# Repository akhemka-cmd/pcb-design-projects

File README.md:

# PCB Design Projects

A portfolio of my PCB designs — automotive LiDAR hardware (Georgia Tech VIP) and an industrial automation controller (SMARK).

| Project | Description | Tool | Status |
|---|---|---|---|
| [`smark-aem-150dc8-eth`](smark-aem-150dc8-eth/) | STM32-based industrial automation controller with Ethernet, isolated ADC front-end, 8× analog + 8× digital inputs | KiCad | Rev 1 |
| [`automotive-lidar/rev1-sprite-hardware`](automotive-lidar/rev1-sprite-hardware/) | "Project Sprite" automotive LiDAR hardware — interface board, motion platform, power supply, scanning mechanism | KiCad | Rev 1 |
| [`automotive-lidar/rev2-vip-spring25`](automotive-lidar/rev2-vip-spring25/) | Automotive LiDAR redesign — 5-ch receiver, IMU, USB hub, interface & power boards | Altium Designer | Rev 2 |

## Opening the projects

- **KiCad projects** (`smark-aem-150dc8-eth`, `rev1-sprite-hardware`): open the `.kicad_pro` file in KiCad 7/8. Symbol/footprint libraries are referenced via the included `sym-lib-table` / `fp-lib-table` (Rev 1 LiDAR) or KiCad's stock libraries (SMARK).
- **Altium project** (`rev2-vip-spring25`): open `AutoLidar_VIP_Spring25.PrjPcb` in Altium Designer.

## Author

Arnav Khemka — Georgia Institute of Technology

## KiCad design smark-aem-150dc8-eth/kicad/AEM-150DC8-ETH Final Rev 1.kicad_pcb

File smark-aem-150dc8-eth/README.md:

# AEM-150DC8-ETH — SMARK Automation Controller

Industrial automation controller board ("AEM Family") designed for SMARK — a STM32-based I/O controller with Ethernet connectivity and an isolated analog front-end.

## Key features

- **MCU:** STM32F407VETx (ARM Cortex-M4)
- **Ethernet:** LAN8742A PHY + Hanrun HR911105A RJ45 jack, RMII interface (`ETHER_RMII.kicad_sch`)
- **Isolated ADC front-end** (`adc ext.kicad_sch`): ADS1115 16-bit ADC, ISO1540 I2C isolator, RO-0505S isolated DC-DC, LTV-217 optocouplers
- **Signal conditioning:** MCP6004 quad op-amps
- **I/O:** 8× analog inputs (AI1–AI8) and 8× digital inputs (DI1–DI8) on screw terminal blocks
- **Comms & UI:** RS-485 transceiver, 16×4 character LCD, buzzer, status LED
- **Board:** 2-layer, KiCad

## Files

| File | Contents |
|---|---|
| `kicad/AEM-150DC8-ETH Final Rev 1.kicad_pro` | KiCad project — open this |
| `kicad/AEM-150DC8-ETH Final Rev 1.kicad_sch` | Top-level schematic |
| `kicad/AEM-150DC8-ETH Final Rev 1.kicad_pcb` | Board layout |
| `kicad/ETHER_RMII.kicad_sch` | Ethernet PHY hierarchical sheet |
| `kicad/adc ext.kicad_sch` | Isolated external ADC hierarchical sheet |
| `kicad/AEM-150DC8-ETH Final BOM.csv` | Bill of materials |
| `kicad/AEM-150DC8-ETH Final BOM LCSC.csv` | LCSC/JLCPCB assembly BOM |
| `docs/board-3d-render.png` | 3D render of the board |

## Design notes

- Analog and digital sections are partitioned on the layout, with the ADC front-end galvanically isolated from the MCU side.
- The LCSC BOM is set up for JLCPCB assembly (0603 passives throughout).

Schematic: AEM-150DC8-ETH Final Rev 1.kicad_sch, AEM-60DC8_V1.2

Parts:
BZ1: Buzzer; QMB09B03; MPN QMB-09B-03; LCSC_Part C96256
C1: 10uF/50V; C0805; MPN CL21A106KBYQNNE; LCSC_Part C2932476
C2: 100uF/63V; C_Elec_10x10.2; MPN RT1J101M1010; LCSC_Part C280414
C3, C56, C57, C58: 1uF/10V; C0603; MPN CGA0603X5R105K100JT; LCSC_Part C20070307
C4, C5, C6, C7, C9, C13, C14, C15, C16, C19, C20, C21, C22, C24, C27, C28, C29, C30, C31, C32, C33, C34, C37, C38, C39, C40, C42, C48, C54, C55, C59, C60: 0.1uF; C0603
C8, C10, C11: 1uF/100V; C1206; MPN CL31B105KCHNNNE; LCSC_Part C13832
C12: 4.7nF/50V; C0805; MPN TCC0805X7R472M500DT; LCSC_Part C5375827
C17: 6.8pF/100V; C0603; MPN AC0603CRNPO0BN6R8; LCSC_Part C6117724
C18: 100nF/25V; C0805; MPN CGA0805X7R104K250KT; LCSC_Part C36911366
C23, C26, C35: 47uF/10V; C1206; MPN TCC1206X5R476K100HT; LCSC_Part C5449028
C25, C36: 10uF/16V; C0805; MPN GRM21BR61C106KE15L; LCSC_Part C77075
C41, C43: 2.2uF; C0402
C45, C46: 12pF; C0603; MPN CGA0603C0G120J500JT; LCSC_Part C45359931
C65, C66, C69, C70: 0.1uF; C0402; MPN CGA0402X7R104M500GT; LCSC_Part C36911361
C67: 4.7uF/25V; C0402; MPN CGA0402X5R475M250GT; LCSC_Part C6119795
C72: 10uF/16V; C0603; MPN GRM21BR61C106KE15L; LCSC_Part C77075
C73, C74: 12pF; C0402; MPN CGA0603C0G120J500JT; LCSC_Part C45359931
C79, C81: 1uF; C0402; MPN CGA0402X7R104M500GT; LCSC_Part C36911361
C80: 100nF; C0402; MPN CGA0402X7R104M500GT; LCSC_Part C36911361
D1, D2, D5, D7, D9, D10, D15, D16: LED; LED_0603_1608Metric; MPN XL-1608SURC-06; LCSC_Part C965799
D3: SMF33A; SOD-123F; MPN SMF33A; LCSC_Part C2943834
D4: SMAJ30A; D_SMA; MPN SMAJ30A; LCSC_Part C908776
D6: B340A-13-F; DO-214AC; MPN B340A-13-F; LCSC_Part C85098
D8: BZT52C10; D_SOD-123F; MPN BZT52C10V; LCSC_Part C5182291
D11, D12, D13, D14, D37, D38, D39, D40: SMAJ160A; DO-214AC; MPN SMAJ160A; LCSC_Part C2984997
D17, D18, D19, D20, D21, D22, D23, D24: SMF24A; SOD-123F; MPN SMF24A; LCSC_Part C2857282
D25, D26, D27, D28, D42, D43, D44, D45: LESD5Z3.3T1G; SOD-523; MPN LESD5Z3.3T1G; LCSC_Part C136161
D29, D30, D31, D32, D33, D34, D35, D36: 1N4007W; SOD-123F; MPN 1N4007W; LCSC_Part C7528871
D41: SS54; DO-214AC; MPN UMW SS54A; LCSC_Part C2988633
D46: LED; LED_0805_2012Metric; MPN XL-2012SURC; LCSC_Part C22371391
D47: SM712; SOT-23-3; MPN SM712-02HTG; LCSC_Part C172881
D48, D51, D53: SMF3.3A; SOD-123F; MPN SMF3.3A; LCSC_Part C37331473
D49: SMAJ26A; DO-214AC; MPN SMAJ26A; LCSC_Part C42370520
D50: PRTR5V0U2F; FNL6_SOT886_NEX; MPN PRTR5V0U2F,115; LCSC_Part C478118
D52: DSS34; SOD-123F; MPN DSS34; LCSC_Part C49023416
D54: 1N4148WS; SOD-323F; MPN 1N4148WS; LCSC_Part C917117
D55: XL-5050RGBC; LED_RGB_5050-6; MPN XL-5050RGBC; LCSC_Part C2843868
DS1: LCD 16x4; NHD0416BZFLGBW; MPN CH1604C
H2, H3: MountingHole; MountingHole_2.5mm; MPN HP-20M3*20; LCSC_Part C123695
H5, H6, H7, H8: MountingHole; MountingHole_3.5mm; not fitted
J1: Conn_01x02; JST_B2B-XH-A; MPN HX-XH2.54-2PZZ; LCSC_Part C42391660
J2: Screw_Terminal_01x10; TerminalBlock_10P_P5mm; MPN MX128-5.0-10P-GN01-Cu-Y-A; LCSC_Part C5290375
J3: Screw_Terminal_01x09; TerminalBlock_9P_P5mm; MPN MX128-5.0-09P-GN01-Cu-Y-A; LCSC_Part C5290374
J5: CONN_03X2SHROUD; CONN_2X3-SHROUDED_HEADER; MPN 321006SG0ABK00A01; LCSC_Part C601936
J6: Screw_Terminal_01x04; TerminalBlock_Phoenix_MKDS-1,5-4-5.08_1x04_P5.08mm_Horizont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
J7: USB_C_Receptacle_USB2.0_16P; USB_C_Receptacle_G-Switch_GT-USB-7010ASV; MPN HYCW498-USBC16-735B; LCSC_Part C42400252
J8: Screw_Terminal_01x02; TerminalBlock_2P_P5.08mm; MPN MX128L-5.08-02P-GN01-Cu-Y-A; LCSC_Part C5188473
J9: Screw_Terminal_01x02; JST_B2B-XH-A
J10: Screw_Terminal_01x02; CONN2_M22-2010_HRW
L1: MNR8065T100MT; IND_SRN8040TA
Q1: ZXMP6A18KTC; TO-252AA_MOSFET; MPN ZXMP6A18KTC; LCSC_Part C154895
Q5: ES5N10S‎; SOT-23-3; MPN ES5N10S‎; LCSC_Part C39832206
Q6, Q10: BC847; SOT-23-3; MPN BC847C,215; LCSC_Part C8664
Q8, Q13, Q14, Q15, Q16: BSS138; SOT-23-3; MPN BSS138; LCSC_Part C3289984
Q9: DMP4065S-7; SOT-23-3; MPN DMP4065S-7; LCSC_Part C182476
Q11, Q12: 2N7002DW-7-F; SOT-363; MPN 2N7002DW-7-F; LCSC_Part C83571
R1, R45, R46, R47, R48, R49, R50, R51, R52, R71, R84, R85, R87, R90, R94, R97, R99, R102, R110: 10K; R0603; MPN FRC0603J103 TS; LCSC_Part C2930027
R2: 100K; R_0603_1608Metric; MPN FRC0603F1003TS; LCSC_Part C2906980
R3, R5, R9, R58, R62, R64: 1K; R0805; MPN ERJ-HP6F1001V; LCSC_Part C4264406
R6: 1K/1%; R0805; MPN ERJ-HP6F1001V; LCSC_Part C4264406
R7, R11, R134: 470K; R1206
R8, R10, R12: 20.5K; R0805; MPN ERJPB6B1002V; LCSC_Part C161788
R13: 470K/0.1%; R1206
R14: 20.5K/0.1%; R0805; MPN ERJPB6B1002V; LCSC_Part C161788
R15, R16, R17, R18, R19, R20, R21, R22: 3K; R0603; MPN FRC0603J302 TS; LCSC_Part C2907162
R23, R24, R25, R26, R27, R28, R29, R30: 1M; R0603; MPN FRC0603J105 TS; LCSC_Part C2907115
R31, R32, R33, R34, R35, R36, R37, R38, R104, R105, R106: 1K; R0603; MPN FRC0603J102 TS; LCSC_Part C2907113
R39: 28.7K; R0805; MPN FRC0805F2872TS; LCSC_Part C2933395
R40, R41, R42, R43, R67, R68, R69, R70, R88, R107, R109, R112: 100R; R0603; MPN FRC0603J101 TS; LCSC_Part C2907089
R44: 191K; R0603; MPN FRC0603F1913TS; LCSC_Part C2974031
R53, R54, R55, R56, R113, R114, R116, R117, R118, R119, R135: 470K; R_1206_3216Metric
R57, R59, R61: 20.5K; R_0805_2012Metric; MPN ERJPB6B1002V; LCSC_Part C161788
R60: 1K; R_0805_2012Metric; MPN ERJ-HP6F1001V; LCSC_Part C4264406
R63: 20.5K; R_0805_2012Metric_Pad1.20x1.40mm_HandSolder; MPN ERJPB6B1002V; LCSC_Part C161788
R65: 60.4K; R0805; MPN FRC0805F6042TS; LCSC_Part C2933477
R66: 11.5K; R0805; MPN FRC0805F1152TS; LCSC_Part C2933288
R72, R74, R77, R82, R91, R130, R132, R133: 2.2K; R0603; MPN FRC0603J222 TS; LCSC_Part C2907117
R75, R78, R79, R95: 4.7K; R0603; MPN FRC0603J472 TS; LCSC_Part C2907166
R76: 120R; R0603; MPN FRC0603J121 TS; LCSC_Part C2907096
R80, R81: 51R/0.5W; R1206; MPN FRP1206J510 TS; LCSC_Part C7468138
R89: 100K; R0603; MPN FRC0603F1003TS; LCSC_Part C2906980
R92: 22R; R0603; MPN FRC0603J220 TS; LCSC_Part C2907129
R93, R129: 1.5K; R0603; MPN FRC0603J152 TS; LCSC_Part C2907083
R96, R98: 5.1K; R0603; MPN FRC0603J512 TS; LCSC_Part C2907114
R108: 150R; R0603; MPN FRC0603F1500TS; LCSC_Part C2906994
R111: 100R; R0805; MPN FRS0805J101 TS; LCSC_Part C7467912
R115: 470K/0.1%; R_1206_3216Metric
R124: 0R; R0603
R137, R138: 2.2K; R0603
R139, R140, R141: 10K; R0603
RV1: 10K; Pot_TRIM_3362P-1-103LF; MPN 3362P-1-103LF; LCSC_Part C118956
SW1, SW3: KH-303015-AJ; SW4_CS1210F260_3.4mm; MPN KH-303015-AJ; LCSC_Part C530668
SW2: SW_DIP_x04; MPN DA-04RP; LCSC_Part C129023
Switch_PCB1: Switch_PCB
TP1: GND; TestPoint_Pad_D1.0mm; not fitted
TP2: +5V; TestPoint_Pad_D1.0mm; not fitted
TP3: +3V3; TestPoint_Pad_D1.0mm; not fitted
U1: MC7805BDTRKG-GK; TO-252-2; MPN MC7805BDTRKG-GK; LCSC_Part C46061589
U2, U14: MCP6004; SOIC-14; MPN MCP6004T-I/SL; LCSC_Part C20627194
U3, U4: LTV-847S; SMDIP-16_W9.53mm; MPN LTV-847S; LCSC_Part C114599
U5: TPS54360DDAR; TI_SO-PowerPAD-8_ThermalVias; MPN TPS54360DDAR; LCSC_Part C44377
U6, U7, U8, U9, U10, U11, U12, U13: 74LVC1G14GW; TSSOP-5; MPN 74LVC1G14GW,125; LCSC_Part C19829653
U15: NCP1117ST33T3G; SOT-223-3_TabPin2; MPN NCP1117ST33T3G; LCSC_Part C26537
U16: CAT24C16TDI-GT3; SOT-753; MPN CAT24C16TDI-GT3; LCSC_Part C605329
U17: THVD1500DR; SOIC-8N_127P599X175; MPN THVD1500DR; LCSC_Part C191014
U20: W25N512GVEIG; SON127P800X600X80-9N-D; MPN W25N512GVEIG; LCSC_Part C3024446
U21: W25Q512JVSSIQ; SOIC-8N_127P790X216; not fitted
U22: PCA9557PW; TSSOP-16; MPN PCA9557PW,118; LCSC_Part C141380
U23: STM32F407VETx; LQFP-100_14x14mm_P0.5mm; MPN STM32F407VET6; LCSC_Part C28730
Y2: M16000E134; SMD3225-4P; MPN M16000E134; LCSC_Part C258943
Y4: SMD_CRYSTAL32.768; XTAL_NX2012SA-32.768K-STD-MUB-1; MPN NX2012SA-32.768KHZ-STD-MUB-2; LCSC_Part C891748

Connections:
10-30VDC: C2.1, C8.1, C10.1, C11.1, D8.1 (K), Q1.2 (S), U5.2 (VIN)
+3.3V: C65.1, C66.1, C67.1, C69.1, C70.1, C79.1, C80.1, C81.1, R124.2, U23.11 (VDD), U23.19 (VDD), U23.21 (VREF+), U23.22 (VDDA), U23.28 (VDD), U23.50 (VDD), U23.75 (VDD), U23.100 (VDD)
+3.3VA: C9.1, C24.1, U2.4 (V+), U14.4 (V+); also elsewhere on the board
+3V3: C27.1, C28.1, C29.1, C30.1, C31.1, C32.1, C33.1, C34.1, C36.1, C42.1, C54.2, J1.2, Q8.1 (G), Q13.1 (G), Q14.1 (G), Q15.1 (G), Q16.1 (G), R45.1, R46.1, R47.1, R48.1, R49.1, R50.1, R51.1, R52.1, R72.1, R77.1, R84.1, R87.1, R90.2, R91.1, R97.2, R99.2, R124.1, R132.2, R133.1, R139.1, R140.1, R141.1, SW1.3, SW1.4, TP3.1 (1_1), U6.5 (VCC), U7.5 (VCC), U8.5 (VCC), U9.5 (VCC), U10.5 (VCC), U11.5 (VCC), U12.5 (VCC), U13.5 (VCC), U15.2 (VO), U16.4 (V_{CC}), U20.7 (/HOLD_(IO3)), U20.8 (VCC), U21.7 (/HOLD_OR_/RESET_(IO3)), U21.8 (VCC); also elsewhere on the board
+5V: BZ1.1 (+), C23.1, C25.1, C26.1, C35.1, C48.1, C59.1, C60.1, D54.1 (K), D55.4 (GA), D55.5 (RA), D55.6 (BA), DS1.2 (VDD), L1.2, Q9.2 (S), R65.1, R71.1, R74.1, R75.1, R78.1, R82.1, R94.2, R95.1, R102.1, R111.1, R137.1, R138.1, RV1.1, TP2.1 (1_1), U15.3 (VI), U17.8 (VCC), U22.16 (VDD); also elsewhere on the board
+5V_DI: C3.1, D1.2 (A), D2.2 (A), D5.2 (A), D7.2 (A), D9.2 (A), D10.2 (A), D15.2 (A), D16.2 (A), R23.1, R24.1, R25.1, R26.1, R27.1, R28.1, R29.1, R30.1, U1.3 (OUT), U3.1, U3.3, U3.5, U3.7, U4.1, U4.3, U4.5, U4.7
AI1: C13.1, R40.1; also elsewhere on the board
AI2: C14.1, R41.1; also elsewhere on the board
AI3: C15.1, R42.1; also elsewhere on the board
AI4: C16.1, R43.1; also elsewhere on the board
AI5: C40.1, R70.1; also elsewhere on the board
AI6: C37.1, R67.1; also elsewhere on the board
AI7: C38.1, R68.1; also elsewhere on the board
AI8: C39.1, R69.1; also elsewhere on the board
AI-1: D11.1 (A1), J3.2, R113.1
AI-2: D12.1 (A1), J3.3, R135.1
AI-3: D13.1 (A1), J3.4, R114.1
AI-4: D14.1 (A1), J3.5, R115.1
AI-5: D38.1 (A1), J3.6, R116.1
AI-6: D39.1 (A1), J3.7, R117.1
AI-7: D40.1 (A1), J3.8, R118.1
AI-8: D37.1 (A1), J3.9, R119.1
BOOT0: R85.1, SW1.1, SW1.2, U23.94 (BOOT0)
B_LED: R104.1, U23.2 (PE3)
Buzzer: R129.1, U23.63 (PC6)
CLK+: C46.1, U23.12 (PH0), Y2.1
CLK-: C45.1, U23.13 (PH1), Y2.3
COL1: U23.17 (PC2); also elsewhere on the board
COL2: U23.18 (PC3); also elsewhere on the board
COM-DO_PLC-0V: D49.2 (A2), J8.1, Q5.2 (S)
D4: DS1.11 (DB4), U22.11 (IO4)
D5: DS1.12 (DB5), U22.12 (IO5)
D6: DS1.13 (DB6), U22.13 (IO6)
D7: DS1.14 (DB7), U22.14 (IO7)
D+: D50.3, J7.A6 (D+), J7.B6 (D+)
D-: D50.1, J7.A7 (D-), J7.B7 (D-)
DI1: D21.1 (A1), J2.3, R15.2
DI1_LED: D1.1 (K), D29.2 (A), R23.2, R31.2
DI2: D17.1 (A1), J2.4, R16.2
DI2_LED: D2.1 (K), D30.2 (A), R24.2, R32.2
DI3: D22.1 (A1), J2.5, R17.2
DI3_LED: D5.1 (K), D31.2 (A), R25.2, R33.2
DI4: D18.1 (A1), J2.6, R18.2
DI4_LED: D7.1 (K), D32.2 (A), R26.2, R34.2
DI5: D23.1 (A1), J2.7, R19.2
DI5_LED: D9.1 (K), D33.2 (A), R27.2, R35.2
DI6: D19.1 (A1), J2.8, R20.2
DI6_LED: D10.1 (K), D34.2 (A), R28.2, R36.2
DI7: D24.1 (A1), J2.9, R21.2
DI7_LED: D15.1 (K), D35.2 (A), R29.2, R37.2
DI8: D20.1 (A1), J2.10, R22.2
DI8_LED: D16.1 (K), D36.2 (A), R30.2, R38.2
DI-1: R45.2, U3.16, U6.2
DI-2: R46.2, U3.14, U7.2
DI-3: R47.2, U3.12, U8.2
DI-4: R48.2, U3.10, U9.2
DI-5: R49.2, U4.16, U10.2
DI-6: R50.2, U4.14, U11.2
DI-7: R51.2, U4.12, U12.2
DI-8: R52.2, U4.10, U13.2
DIP_S1: R141.2, SW2.2B, U23.81 (PD0)
DIP_S2: R140.2, SW2.3B, U23.82 (PD1)
DIP_S3: R139.2, SW2.4B, U23.83 (PD2)
DI_1: U6.4, U23.39 (PE8)
DI_2: U7.4, U23.40 (PE9)
DI_3: U8.4, U23.41 (PE10)
DI_4: U9.4, U23.54 (PB15)
DI_5: U10.4, U23.43 (PE12)
DI_6: U11.4, U23.44 (PE13)
DI_7: U12.4, U23.45 (PE14)
DI_8: U13.4, U23.46 (PE15)
DO-ALARM: D49.1 (A1), J8.2, R92.2
DO_1: R88.1, U23.88 (PD7)
E: DS1.6 (E), U22.7 (IO1)
FLASH_CS: U20.1 (/CS), U21.1 (/CS), U23.77 (PA15)
Field_VTG: D3.1 (A1), D6.2 (A), J2.2
GND: C2.2, C8.2, C10.2, C11.2, C12.2, C17.2, C23.2, C25.2, C26.2, C27.2, C28.2, C29.2, C30.2, C31.2, C32.2, C33.2, C34.2, C35.2, C36.2, C41.2, C42.2, C43.2, C45.2, C46.2, C48.2, C54.1, C55.1, C56.2, C57.2, C58.2, C59.2, C60.2, C65.2, C66.2, C67.2, C69.2, C70.2, C72.1, C73.2, C74.2, C79.2, C80.2, C81.2, D4.2 (A2), D41.2 (A), D46.1 (K), D47.3 (common), D48.2 (A2), D50.2, D51.2 (A2), D53.2 (A2), DS1.1 (VSS), J5.6, J6.3, J7.A1 (GND), J7.A12 (GND), J7.B1 (GND), J7.B12 (GND), J7.S1 (SHIELD), J9.1, J10.1, Q10.2 (E), Q11.1 (S1), Q11.4 (S2), Q12.1 (S1), Q12.4 (S2), R1.2, R2.2, R44.2, R66.2, R79.2, R85.2, R89.2, R93.1, R96.1, R98.1, R110.1, R130.2, RV1.3, SW2.2A, SW2.3A, SW2.4A, SW3.3, SW3.4, Switch_PCB1.4 (GND), TP1.1 (1_1), U3.9, U3.11, U3.13, U3.15, U4.9, U4.11, U4.13, U4.15, U5.7 (GND), U5.9 (GNDPAD), U6.3 (GND), U7.3 (GND), U8.3 (GND), U9.3 (GND), U10.3 (GND), U11.3 (GND), U12.3 (GND), U13.3 (GND), U15.1 (GND), U16.2 (V_{SS}), U17.5 (GND), U20.4 (GND), U20.9 (EP), U21.4 (GND), U22.3 (A0), U22.4 (A1), U22.5 (A2), U22.8 (VSS), U23.10 (VSS), U23.20 (VSSA), U23.27 (VSS), U23.74 (VSS), U23.99 (VSS), Y2.2, Y2.4; also elsewhere on the board
GND2: C1.2, C3.2, D3.2 (A2), D17.2 (A2), D18.2 (A2), D19.2 (A2), D20.2 (A2), D21.2 (A2), D22.2 (A2), D23.2 (A2), D24.2 (A2), J2.1, U1.2 (GND)
GND_ISO: C4.2, C5.2, C6.2, C7.2, C9.2, C13.2, C14.2, C15.2, C16.2, C19.2, C20.2, C21.2, C22.2, C24.2, C37.2, C38.2, C39.2, C40.2, D11.2 (A2), D12.2 (A2), D13.2 (A2), D14.2 (A2), D25.2 (A2), D26.2 (A2), D27.2 (A2), D28.2 (A2), D37.2 (A2), D38.2 (A2), D39.2 (A2), D40.2 (A2), D42.2 (A2), D43.2 (A2), D44.2 (A2), D45.2 (A2), J3.1, R8.2, R10.2, R12.2, R14.2, R57.2, R59.2, R61.2, R63.2, U2.11 (V-), U14.11 (V-); also elsewhere on the board
G_LED: R106.1, U23.1 (PE2)
I2C1_SCL: Q16.2 (S), R133.2, U16.1 (SCL), U23.95 (PB8)
I2C1_SCL_5V: Q16.3 (D), R137.2, U22.1 (SCL)
I2C1_SDA: Q13.2 (S), R132.1, U16.3 (SDA), U23.93 (PB7)
I2C1_SDA_5V: Q13.3 (D), R138.2, U22.2 (SDA)
IO_RESET: Q8.2 (S), R91.2, U23.5 (PE6)
IO_RESET_5V: Q8.3 (D), R95.2, U22.15 (~RESET)
LCD_Backlight: R112.1, U23.92 (PB6)
NRST: C55.2, J5.4, R87.2, SW3.1, SW3.2, U23.14 (NRST)
NTC: J1.1, R1.1, U23.65 (PC8)
unnamed: BZ1.2 (-), D54.2 (A), Q10.3 (C)
unnamed: C12.1, R39.2
unnamed: D4.1 (A1), J6.4, Q1.3 (D)
unnamed: C1.1, D6.1 (K), U1.1 (IN)
unnamed: D8.2 (A), Q1.1 (G), R2.1
unnamed: C4.1, D25.1 (A1), R3.1, U2.3 (+)
unnamed: C5.1, D26.1 (A1), R9.1, U2.5 (+)
unnamed: C6.1, D27.1 (A1), R5.1, U2.10 (+)
unnamed: C7.1, D28.1 (A1), R6.1, U2.12 (+)
unnamed: D29.1 (K), R15.1
unnamed: D30.1 (K), R16.1
unnamed: D31.1 (K), R17.1
unnamed: D32.1 (K), R18.1
unnamed: D33.1 (K), R19.1
unnamed: D34.1 (K), R20.1
unnamed: D35.1 (K), R21.1
unnamed: D36.1 (K), R22.1
unnamed: C18.1, D41.1 (K), L1.1, U5.8 (SW)
unnamed: C19.1, D42.1 (A1), R60.1, U14.3 (+)
unnamed: C20.1, D43.1 (A1), R62.1, U14.5 (+)
unnamed: C21.1, D44.1 (A1), R64.1, U14.10 (+)
unnamed: C22.1, D45.1 (A1), R58.1, U14.12 (+)
unnamed: D46.2 (A), R71.2
unnamed: D52.1 (K), J7.A4 (VBUS), J7.A9 (VBUS), J7.B4 (VBUS), J7.B9 (VBUS)
unnamed: D55.1 (BK), R107.2
unnamed: D55.3 (GK), R109.2
unnamed: D55.2 (RK), R108.2
unnamed: DS1.15 (LED+), R111.2
unnamed: DS1.16 (LED-), Q12.3 (D2)
unnamed: DS1.3 (V0), RV1.2
unnamed: J7.A5 (CC1), R96.2
unnamed: J7.B5 (CC2), R98.2
unnamed: C72.2, J9.2, J10.2, U23.6 (VBAT)
unnamed: Q5.3 (D), R92.1
unnamed: Q5.1 (G), R88.2, R89.1
unnamed: Q6.3 (C), Q9.1 (G), R94.1
unnamed: Q6.2 (E), R93.2
unnamed: Q10.1 (B), R129.2
unnamed: Q11.6 (D1), R108.1
unnamed: Q11.2 (G1), R105.2
unnamed: Q11.3 (D2), R107.1
unnamed: Q11.5 (G2), R104.2
unnamed: Q12.6 (D1), R109.1
unnamed: Q12.2 (G1), R106.2
unnamed: Q12.5 (G2), R110.2, R112.2
unnamed: R3.2, R7.2, R8.1
unnamed: R9.2, R10.1, R134.2
unnamed: R11.1, R114.2
unnamed: R5.2, R11.2, R12.1
unnamed: R6.2, R13.2, R14.1
unnamed: R31.1, U3.2
unnamed: R32.1, U3.4
unnamed: R33.1, U3.6
unnamed: R34.1, U3.8
unnamed: R35.1, U4.2
unnamed: R36.1, U4.4
unnamed: R37.1, U4.6
unnamed: R38.1, U4.8
unnamed: R53.2, R57.1, R58.2
unnamed: R54.2, R59.1, R60.2
unnamed: R55.2, R61.1, R62.2
unnamed: R56.2, R63.1, R64.2
unnamed: R7.1, R113.2
unnamed: R13.1, R115.2
unnamed: R54.1, R116.2
unnamed: R55.1, R117.2
unnamed: R56.1, R118.2
unnamed: R53.1, R119.2
unnamed: R134.1, R135.2
unnamed: R40.2, U2.1, U2.2 (-)
unnamed: R41.2, U2.6 (-), U2.7
unnamed: R42.2, U2.8, U2.9 (-)
unnamed: R43.2, U2.13 (-), U2.14
unnamed: C18.2, U5.1 (BOOT)
unnamed: C17.1, R39.1, U5.6 (COMP)
unnamed: R65.2, R66.1, U5.5 (FB)
unnamed: R44.1, U5.4 (RT/CLK)
unnamed: R70.2, U14.1, U14.2 (-)
unnamed: R67.2, U14.6 (-), U14.7
unnamed: R68.2, U14.8, U14.9 (-)
unnamed: R69.2, U14.13 (-), U14.14
unnamed: R130.1, U16.5 (WP)
unnamed: R76.1, R78.2, R80.1, U17.6 (A)
unnamed: R84.2, U20.3 (/WP_(IO2)), U21.3 (/WP_(IO2))
unnamed: C74.1, U23.8 (PC14), Y4.1
unnamed: C73.1, U23.9 (PC15), Y4.2
unnamed: C41.1, U23.49 (VCAP_1)
unnamed: C43.1, U23.73 (VCAP_2)
PWRC_USB: Q6.1 (B), U23.69 (PA10)
RMII_CRS_DV: U23.32 (PA7); also elsewhere on the board
RMII_MDC: U23.16 (PC1); also elsewhere on the board
RMII_MDIO: U23.25 (PA2); also elsewhere on the board
RMII_REF_CLK: U23.24 (PA1); also elsewhere on the board
RMII_RXD0: U23.33 (PC4); also elsewhere on the board
RMII_RXD1: U23.34 (PC5); also elsewhere on the board
RMII_TXD0: U23.51 (PB12); also elsewhere on the board
RMII_TXD1: U23.52 (PB13); also elsewhere on the board
RMII_TX_EN: U23.48 (PB11); also elsewhere on the board
RS: DS1.4 (RS), R102.2, U22.6 (IO0)
RS485-1B_TRO: R76.2, SW2.1B
RS485-1_TRC: R79.1, R81.2, SW2.1A, U17.7 (B)
RS485_1A: D47.1 (A1), J6.1, R80.2
RS485_1B: D47.2 (A2), J6.2, R81.1
RS485_EN: Q14.2 (S), R72.2, U23.4 (PE5)
RS485_EN_5V: Q14.3 (D), R74.2, U17.2 (~RE), U17.3 (DE)
R_LED: R105.1, U23.3 (PE4)
R/W: DS1.5 (R/W), U22.9 (IO2)
SCL2: U23.67 (PA8); also elsewhere on the board
SDA2: U23.66 (PC9); also elsewhere on the board
SPI1_MISO: U20.2 (DO_(IO1)), U21.2 (DO_(IO1)), U23.90 (PB4)
SPI1_MOSI: U20.5 (DI_(ID0)), U21.5 (DI_(ID0)), U23.91 (PB5)
SPI1_SCK: U20.6 (CLK), U21.6 (CLK), U23.89 (PB3)
SWC: J5.1, U23.76 (PA14)
SWD: J5.2, U23.72 (PA13)
U2_RX: J5.3, U23.87 (PD6)
U2_TX: J5.5, U23.86 (PD5)
U3_RX: R75.2, U17.1 (RO), U23.79 (PC11)
U3_TX: Q15.2 (S), R77.2, U23.78 (PC10)
U3_TX_5V: Q15.3 (D), R82.2, U17.4 (DI)
USB_D+: D50.4, U23.71 (PA12)
USB_D-: D50.6, U23.70 (PA11)
USB_VBUS: D50.5, D52.2 (A), Q9.3 (D), U23.68 (PA9)
USW1: C56.1, D48.1 (A1), R90.1, Switch_PCB1.1 (SW1), U23.62 (PD15)
USW2: C57.1, D51.1 (A1), R97.1, Switch_PCB1.2 (SW2), U23.61 (PD14)
USW3: C58.1, D53.1 (A1), R99.1, Switch_PCB1.3 (SW3), U23.60 (PD13)

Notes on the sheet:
NTC
DIP Switch
RTC
DIGITAL OUTPUT
RST SWITCH
ANALOG INPUTS
EEPROM
Programmer
LDO
RS-485
Output: 5V/2A
SPI FLASH
DIGITAL INPUTS
LCD 16x4 DISPLAY
12V/24V
USER SWITCHES
BUZZER
Float to Enable
USB TYPE-C
POWER SUPPLY
MICROCONTROLLER
Change buzzer part no.
Input Supply: 10V-30VDC Output: 5V/2A
I/O Expander
Using as normal GPIO Pin
RGB LED
PWR LED
(PLC +24V)
DO-ALARM
PLC 0V

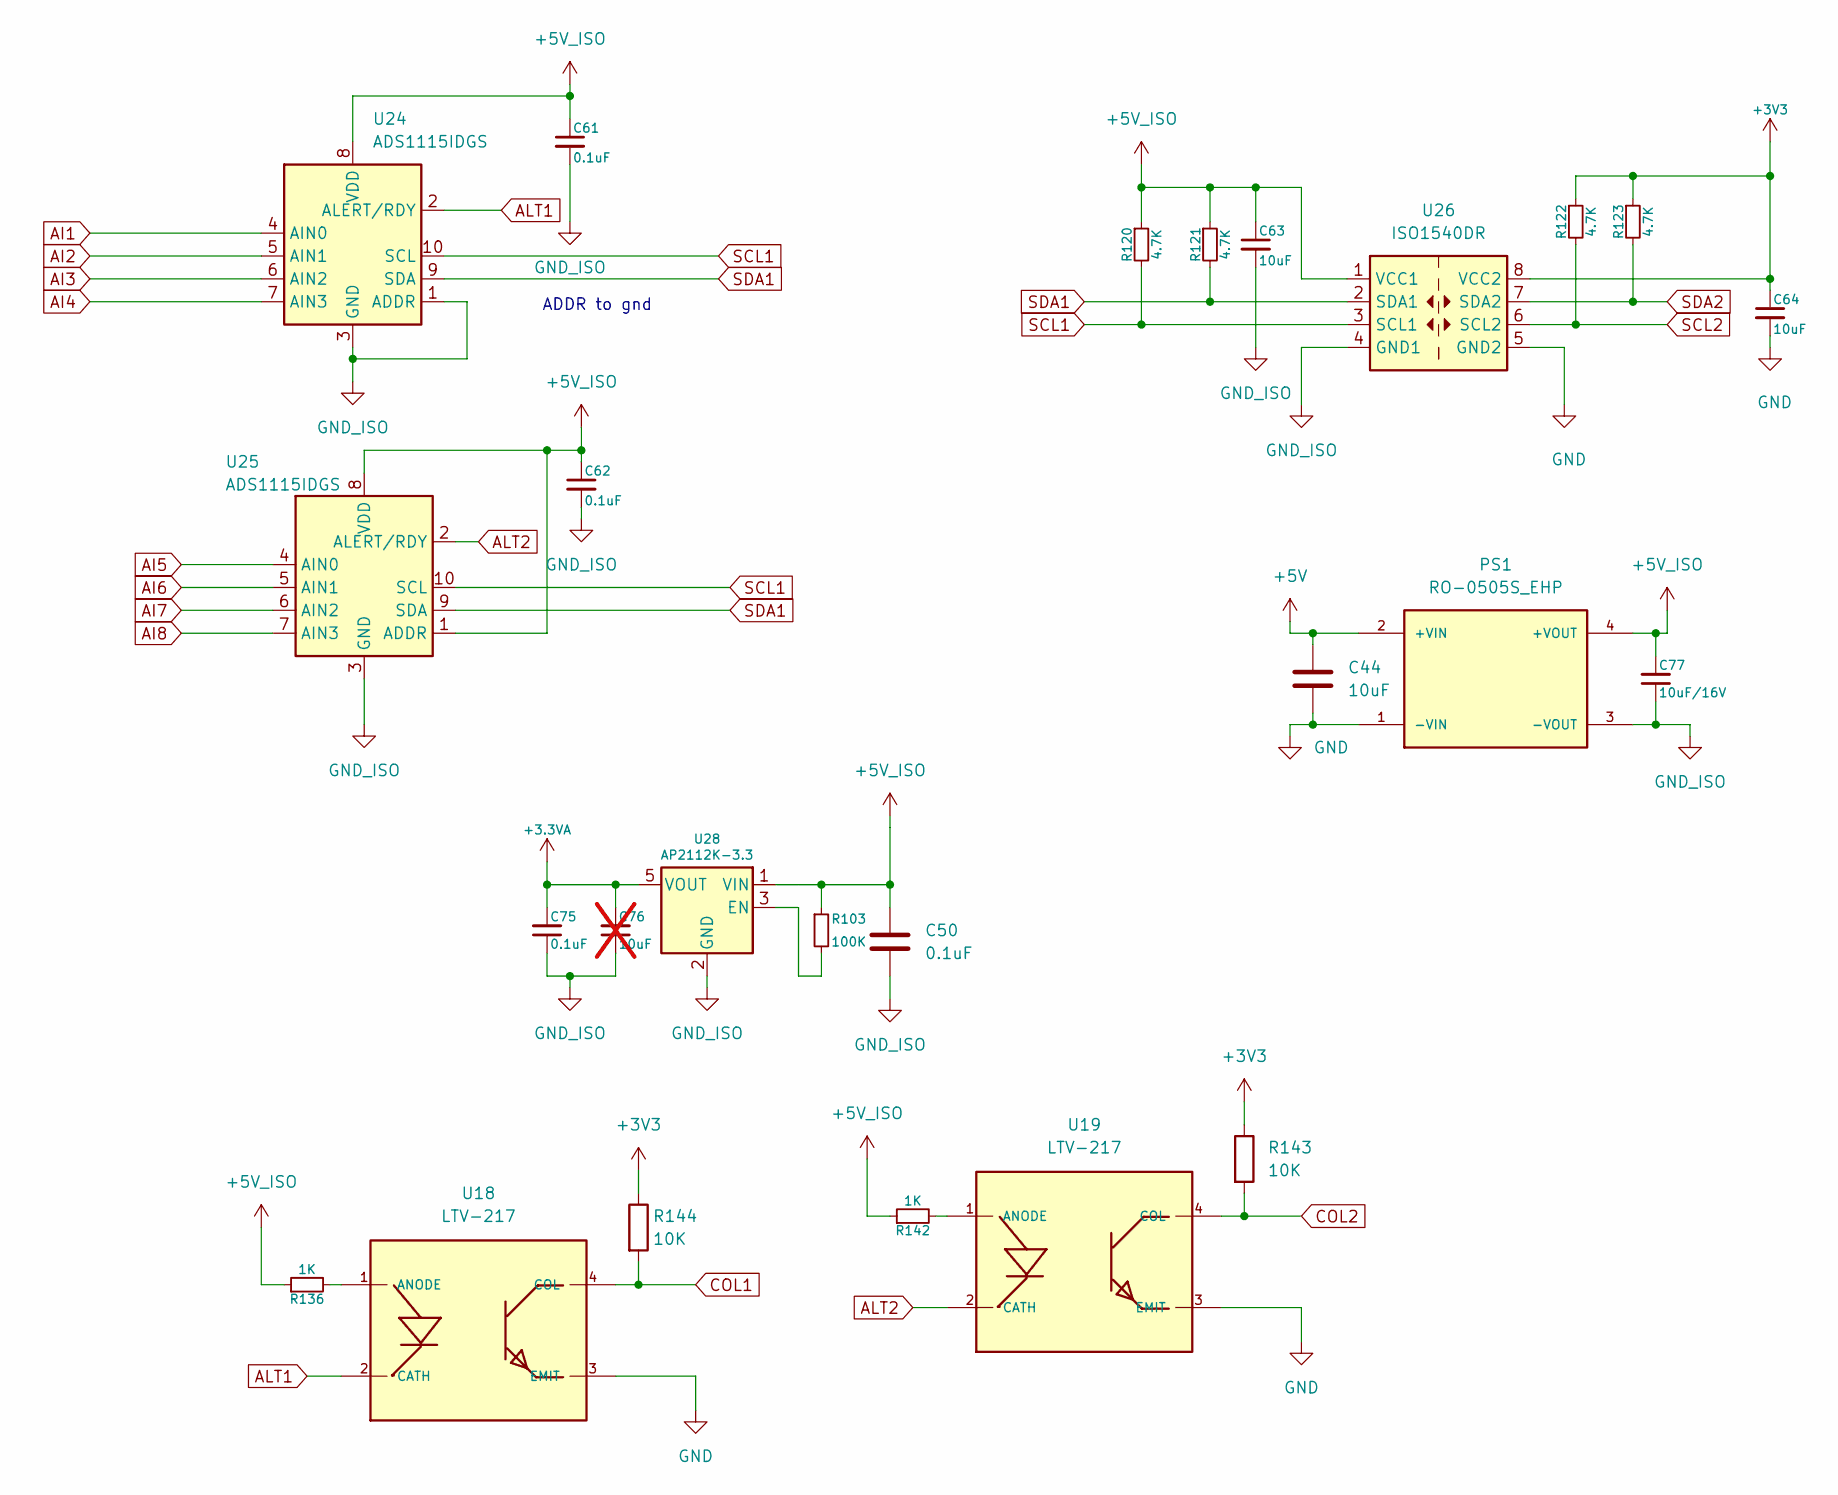
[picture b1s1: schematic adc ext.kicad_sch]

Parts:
C44: 10uF; C0805
C50: 0.1uF; C0805
C61, C75: 0.1uF; C0603
C62: 0.1uF; C0402; MPN CGA0603X7R104K500JT; LCSC_Part C6119867
C63: 10uF; C0603; MPN CGA0603X7R104K500JT; LCSC_Part C6119867
C64: 10uF; C0402; MPN CGA0603X7R104K500JT; LCSC_Part C6119867
C76: 10uF; C0603; MPN FCC0603X106M6R3CT; LCSC_Part C5137483; not fitted
C77: 10uF/16V; C0805; MPN GRM21BR61C106KE15L; LCSC_Part C77075
PS1: RO-0505S_EHP; CONV_RO-0505S_H; PARTREV 1; LCSC_Part C22372152
R103: 100K; R0603; MPN FRC0603F1003TS; LCSC_Part C2906980
R120, R121, R122, R123: 4.7K; R0603; MPN ERJ-HP6F1001V; LCSC_Part C4264406
R136, R142: 1K; R0603; MPN ERJ-HP6F1001V; LCSC_Part C4264406
R143, R144: 10K; R0603
U18: LTV-217; MPN LTV217; DIGIKEY 160-2238-1-ND
U19: LTV-217; MPN LTV-217-C-G; DIGIKEY 160-2238-1-ND
U24, U25: ADS1115IDGS; TSSOP-10_3x3mm_P0.5mm; MPN ADS1115IDGS
U26: ISO1540DR; SOIC-8_3.9x4.9mm_P1.27mm; MPN ISO1540DR
U28: AP2112K-3.3; SOT-753; MPN AP2112K-3.3TRG1; LCSC_Part C23380830

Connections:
+3.3VA: C75.2, C76.2, U28.5 (VOUT); also elsewhere on the board
+3V3: C64.1, R122.1, R123.1, R143.1, R144.1, U26.8 (VCC2); also elsewhere on the board
+5V: C44.1, PS1.2 (+VIN); also elsewhere on the board
+5V_ISO: C50.1, C61.1, C62.1, C63.1, C77.2, PS1.4 (+VOUT), R103.1, R120.1, R121.1, R136.1, R142.1, U24.8 (VDD), U25.1 (ADDR), U25.8 (VDD), U26.1 (VCC1), U28.1 (VIN)
AI1: U24.4 (AIN0); also elsewhere on the board
AI2: U24.5 (AIN1); also elsewhere on the board
AI3: U24.6 (AIN2); also elsewhere on the board
AI4: U24.7 (AIN3); also elsewhere on the board
AI5: U25.4 (AIN0); also elsewhere on the board
AI6: U25.5 (AIN1); also elsewhere on the board
AI7: U25.6 (AIN2); also elsewhere on the board
AI8: U25.7 (AIN3); also elsewhere on the board
ALT1: U18.2 (CATH), U24.2 (ALERT/RDY)
ALT2: U19.2 (CATH), U25.2 (ALERT/RDY)
COL1: R144.2, U18.4 (COL); also elsewhere on the board
COL2: R143.2, U19.4 (COL); also elsewhere on the board
GND: C44.2, C64.2, PS1.1 (-VIN), U18.3 (EMIT), U19.3 (EMIT), U26.5 (GND2); also elsewhere on the board
GND_ISO: C50.2, C61.2, C62.2, C63.2, C75.1, C76.1, C77.1, PS1.3 (-VOUT), U24.1 (ADDR), U24.3 (GND), U25.3 (GND), U26.4 (GND1), U28.2 (GND); also elsewhere on the board
unnamed: R136.2, U18.1 (ANODE)
unnamed: R142.2, U19.1 (ANODE)
unnamed: R103.2, U28.3 (EN)
SCL1: R120.2, U24.10 (SCL), U25.10 (SCL), U26.3 (SCL1)
SCL2: R122.2, U26.6 (SCL2); also elsewhere on the board
SDA1: R121.2, U24.9 (SDA), U25.9 (SDA), U26.2 (SDA1)
SDA2: R123.2, U26.7 (SDA2); also elsewhere on the board

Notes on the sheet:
ADDR to gnd

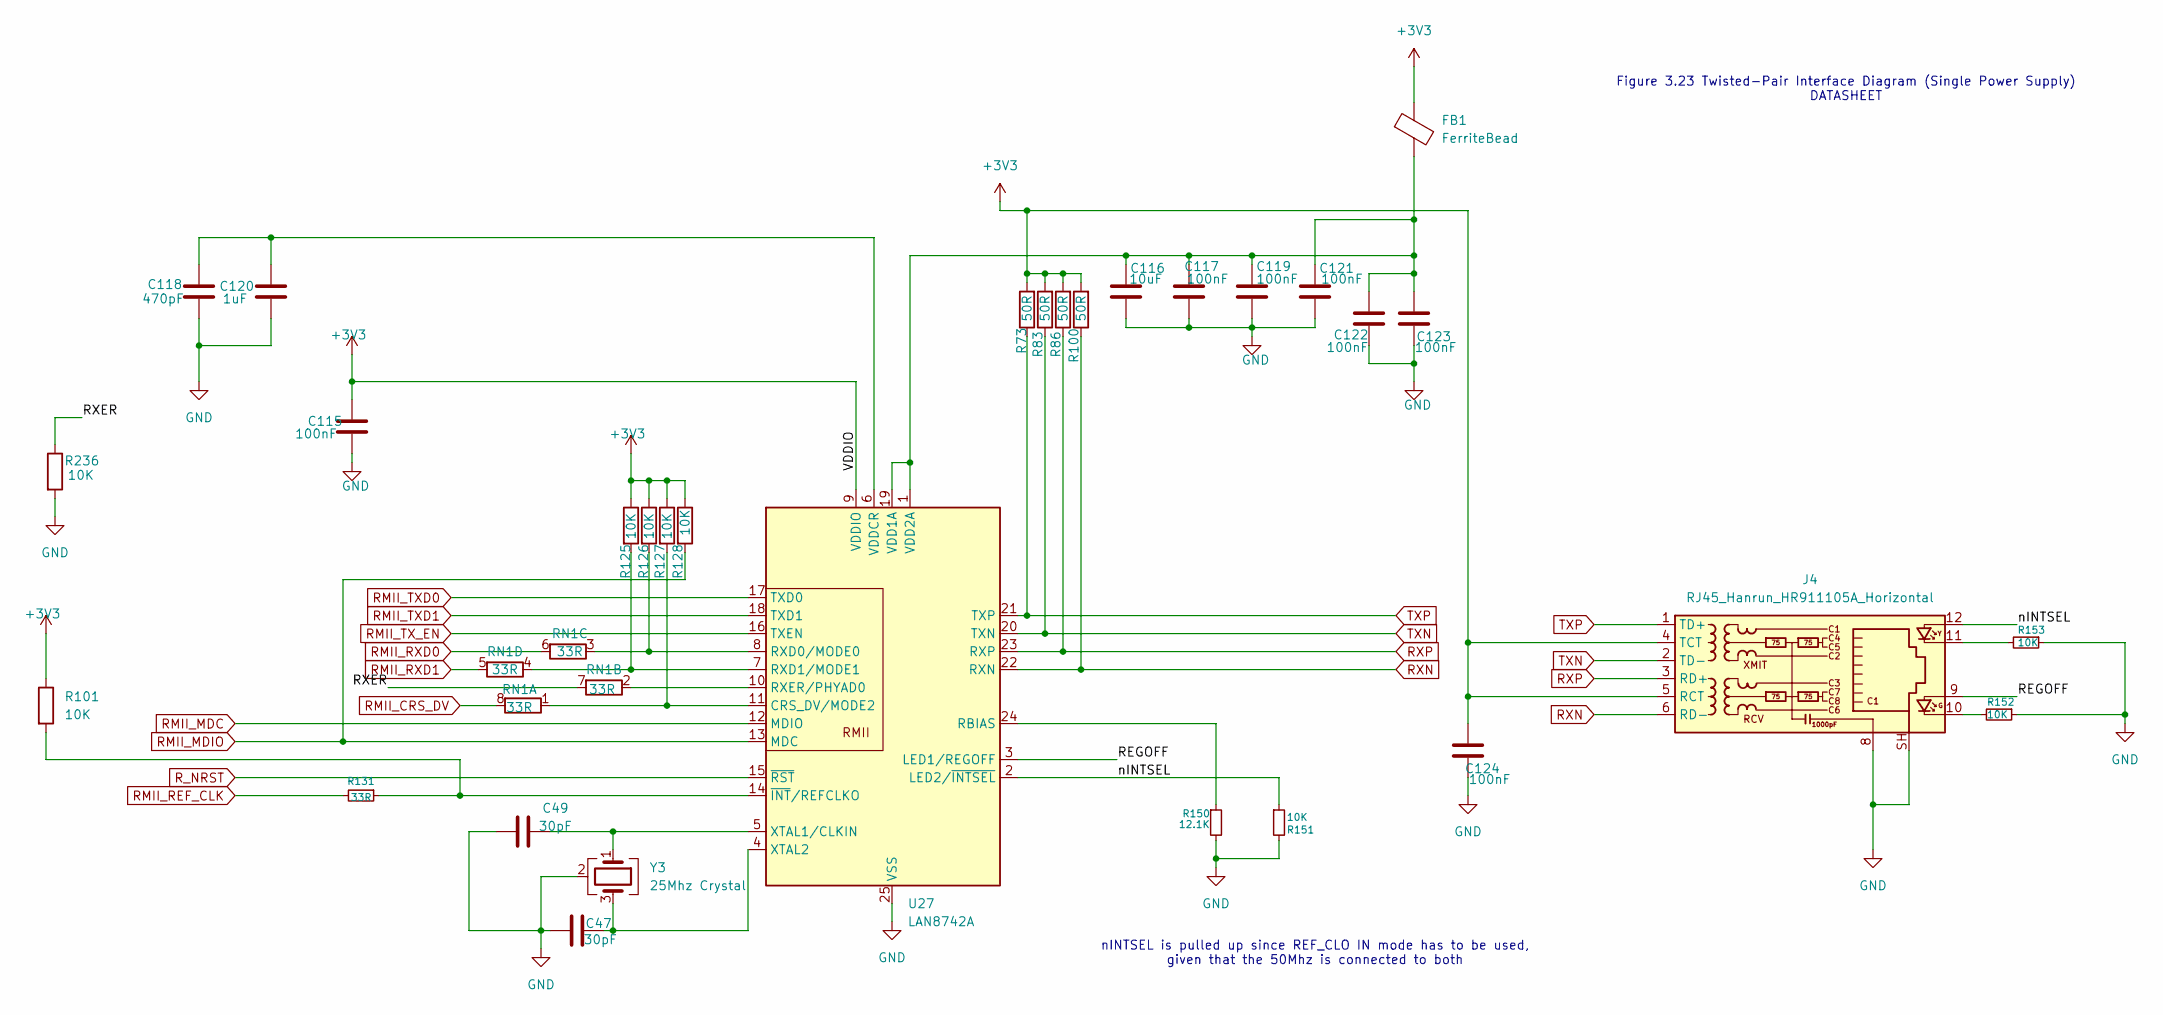
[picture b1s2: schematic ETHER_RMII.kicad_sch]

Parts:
C47, C49: 30pF; C0603
C115, C117, C119, C121, C122, C123: 100nF; C0402
C116: 10uF; C0402; LCSC_Part C6119867
C118: 470pF; C0402
C120: 1uF; C0402
C124: 100nF; C0603
FB1: FerriteBead; R0805
J4: RJ45_Hanrun_HR911105A_Horizontal; MPN HR911105A; LCSC_Part C12074
R73, R83, R86, R100: 50R; R0603
R101, R125, R126, R127, R128, R236: 10K; R0603
R131: 33R; R0603
R150: 12.1K; R_0402_1005Metric
R151: 10K; R_0402_1005Metric
R152, R153: 10K; R0603; MPN FRC0603J472 TS; LCSC_Part C2907166
RN1: 33R; CAT16-1206_8L
U27: LAN8742A; VQFN-24-1EP_4x4mm_P0.5mm_EP2.5x2.5mm_ThermalVias; MPN LAN8742A
Y3: 25Mhz Crystal; Crystal_SMD_3225-4Pin_3.2x2.5mm; MPN X322525MOB4SI; LCSC_Part C9006

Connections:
+3V3: C115.2, C124.2, FB1.1, J4.4 (TCT), J4.5 (RCT), R73.2, R83.2, R86.2, R100.2, R101.1, R125.1, R126.1, R127.1, R128.1, U27.9 (VDDIO); also elsewhere on the board
/Ethernet/REGOFF: J4.9, U27.3 (LED1/REGOFF)
/Ethernet/RXER: R236.1, RN1.7 (R2.2)
/Ethernet/nINTSEL: J4.12, R151.1, U27.2 (LED2/~INTSEL)
GND: C47.1, C49.1, C115.1, C116.1, C117.1, C118.1, C119.1, C120.1, C121.2, C122.1, C123.1, C124.1, J4.8, J4.SH, R150.2, R151.2, R152.1, R153.1, R236.2, U27.25 (VSS), Y3.2 (G), Y3.4 (G); also elsewhere on the board
unnamed: J4.10, R152.2
unnamed: J4.11, R153.2
unnamed: R127.2, RN1.1 (R1.1), U27.11 (CRS_DV/MODE2)
unnamed: RN1.2 (R2.1), U27.10 (RXER/PHYAD0)
unnamed: R126.2, RN1.3 (R3.1), U27.8 (RXD0/MODE0)
unnamed: R125.2, RN1.4 (R4.1), U27.7 (RXD1/MODE1)
unnamed: R150.1, U27.24 (RBIAS)
unnamed: C116.2, C117.2, C119.2, C121.1, C122.2, C123.2, FB1.2, U27.1 (VDD2A), U27.19 (VDD1A)
unnamed: C118.2, C120.2, U27.6 (VDDCR)
unnamed: C49.2, U27.5 (XTAL1/CLKIN), Y3.1
unnamed: C47.2, U27.4 (XTAL2), Y3.3
unnamed: R101.2, R131.1, U27.14 (~INT/REFCLKO)
RMII_CRS_DV: RN1.8 (R1.2); also elsewhere on the board
RMII_MDC: U27.12 (MDIO); also elsewhere on the board
RMII_MDIO: R128.2, U27.13 (MDC); also elsewhere on the board
RMII_REF_CLK: R131.2; also elsewhere on the board
RMII_RXD0: RN1.6 (R3.2); also elsewhere on the board
RMII_RXD1: RN1.5 (R4.2); also elsewhere on the board
RMII_TXD0: U27.17 (TXD0); also elsewhere on the board
RMII_TXD1: U27.18 (TXD1); also elsewhere on the board
RMII_TX_EN: U27.16 (TXEN); also elsewhere on the board
RXN: J4.6 (RD-), R100.1, U27.22 (RXN)
RXP: J4.3 (RD+), R86.1, U27.23 (RXP)
R_NRST: U27.15 (~RST)
TXN: J4.2 (TD-), R83.1, U27.20 (TXN)
TXP: J4.1 (TD+), R73.1, U27.21 (TXP)

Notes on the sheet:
nINTSEL is pulled up since REF_CLO IN mode has to be used, given that the 50Mhz is connected to both
Figure 3.23 Twisted-Pair Interface Diagram (Single Power Supply) DATASHEET
